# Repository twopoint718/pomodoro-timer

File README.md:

Pomodoro Timer
==============

A desktop pomodoro timer.

Peripherals
-----------

- [PCD8544](https://learn.adafruit.com/nokia-5110-3310-monochrome-lcd) 84x48 pixel LCD screen (SPI-based)
- [LSM6DSL](https://www.st.com/resource/en/datasheet/lsm6dsl.pdf) (PDF) iNEMO inertial module always-on 3D accelerometer and 3D gyroscope (I2C)
- TIM (General-purpose timer, onboard)
- GPIO reset button
- UART (onboard)

Code
----

I've either referenced, ported, or otherwise used these open source projects in my own:

- [Adafruit GFX Library](https://github.com/Adafruit/Adafruit-GFX-Library), [BSD License](https://github.com/adafruit/Adafruit-GFX-Library/blob/master/license.txt)
- [STMicroelectronics LSM6DSL accelerometer/gyro driver](https://github.com/STMicroelectronics/stm32-lsm6dsl), [BSD License](https://opensource.org/licenses/BSD-3-Clause)
- [STMicroelectronics HAL code](https://www.st.com/resource/en/user_manual/um1884-description-of-stm32l4l4-hal-and-lowlayer-drivers-stmicroelectronics.pdf) (PDF)
- [8x8 VGA Font](https://github.com/dhepper/font8x8), Public Domain License

Building
--------

Be sure to have already installed the [Arm GNU Toolchain](https://developer.arm.com/tools-and-software/open-source-software/developer-tools/gnu-toolchain).
Then this project can be built by the Makefile in the root directory.

```
make -j
```

Building under Windows
----------------------

TODO

Presentations
-------------

- 8LU Keynote by Chris Wilson: Embedded–From the point of view of a web developer
  [YouTube Link](https://youtu.be/wSTIfWqJzPw)

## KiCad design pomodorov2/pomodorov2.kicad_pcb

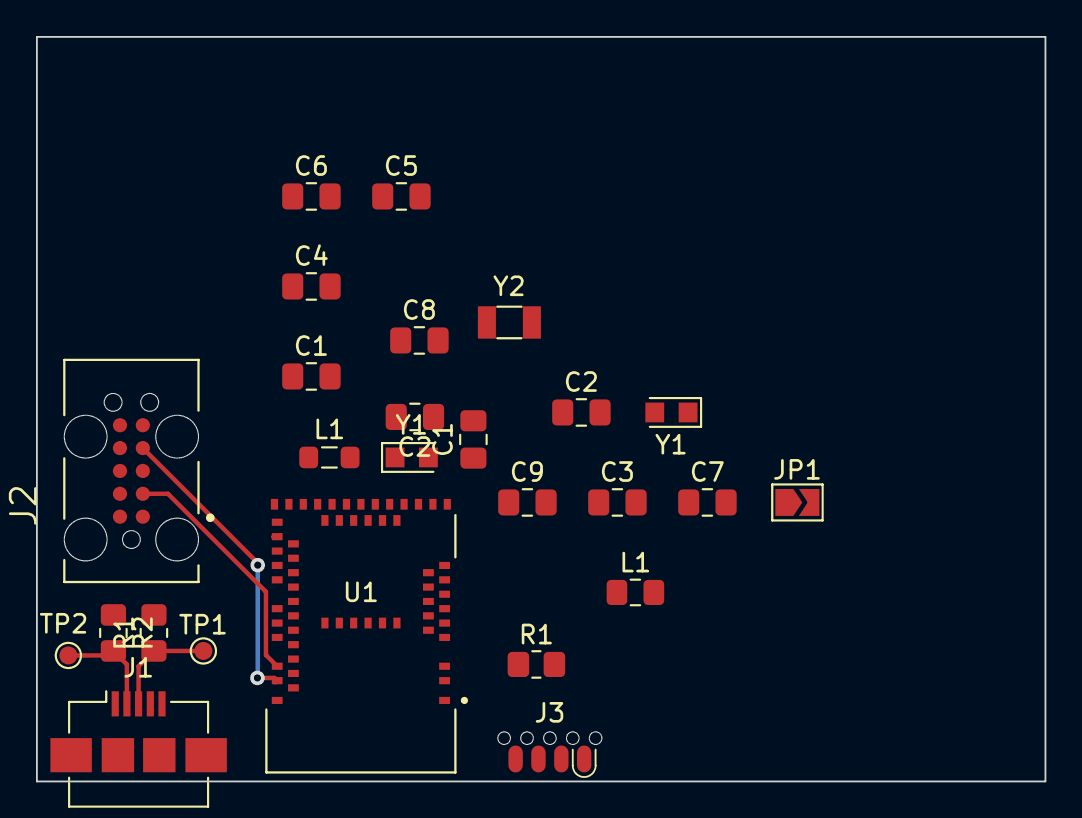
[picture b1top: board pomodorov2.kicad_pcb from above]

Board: 2 copper layers, 56.0 x 41.4 mm, 26 parts (0 on the bottom side), 18 nets.

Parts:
C1, C2, C8, C9: 12pF; C_0805_2012Metric_Pad1.18x1.45mm_HandSolder
C1#2, C2#2: 22pF; C_0805_2012Metric_Pad1.18x1.45mm_HandSolder
C3: 0.8pF; C_0805_2012Metric_Pad1.18x1.45mm_HandSolder
C4, C7: 100nF; C_0805_2012Metric_Pad1.18x1.45mm_HandSolder
C5: 100pF; C_0805_2012Metric_Pad1.18x1.45mm_HandSolder
C6: 1.0uF; C_0805_2012Metric_Pad1.18x1.45mm_HandSolder
J1: USB_B_Micro; USB_Micro-B_Amphenol_10104110_Horizontal
J2: TC2050-IDC; TAG-CONNECT_TC2050-IDC
J3: SOICbite; SOIC_clipProgSmall
JP1: SolderJumper_2_Open; SolderJumper-2_P1.3mm_Open_TrianglePad1.0x1.5mm
L1: 3.9nH; L_0805_2012Metric_Pad1.15x1.40mm_HandSolder
L1#2: 10uH (DNP?); L_0805_2012Metric_Pad1.05x1.20mm_HandSolder
R1: 100K; R_0805_2012Metric_Pad1.20x1.40mm_HandSolder
R1#2, R2: 22; R_0805_2012Metric_Pad1.20x1.40mm_HandSolder
TP1, TP2: TestPoint; TestPoint_Pad_D1.0mm
U1: MDBT50Q-1MV2; XCVR_MDBT50Q-1MV2
Y1: 32MHz; Crystal_SMD_2012-2Pin_2.0x1.2mm_HandSoldering
Y1#2: 32.768kHz; Crystal_SMD_2012-2Pin_2.0x1.2mm_HandSoldering
Y2: 32.768kHz; Crystal_SMD_3215-2Pin_3.2x1.5mm

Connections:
/SWCLK: J2.4, J3.7, U1.53 (SWDCLK)
/SWDIO: J2.2, J3.5, U1.51 (SWDIO)
/SWO: J2.6, J3.6, U1.47 (P1.00/TRACEDATA0)
/USBD+: R1#2.2, U1.35 (D+)
/USBD-: R2.1, U1.34 (D-)
/~RESET: J2.10, J3.8, U1.40 (P0.18/~RESET)
GND: C1.1, C1#2.1, C2.1, C2#2.1, C3.2, C4.1, C5.1, C6.1, C7.2, C8.2, C9.2, J1.5 (GND), J2.3, J2.5, J3.4, JP1.1 (A), U1.1 (GND), U1.2 (GND), U1.15 (GND), U1.33 (GND), U1.55 (GND)
unnamed: C1#2.2, U1.17 (P0.00/XL1), Y1#2.2
unnamed: C2#2.2, U1.18 (P0.01/XL2), Y1#2.1
unnamed: J1.2 (D-), R2.2, TP2.1
unnamed: J1.3 (D+), R1#2.1, TP1.1
unnamed: L1#2.1, U1.31 (DCCH)
unnamed: C8.1, Y2.2
unnamed: C9.1, Y2.1
unnamed: C3.1, L1.2
unnamed: C1.2, Y1.2
unnamed: C2.2, Y1.1
VCC: J2.1, J3.1, L1#2.2, R1.2, U1.28 (VDD), U1.30 (VDDH)

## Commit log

2022-01-02 Ignore compilation artifacts
2022-01-02 Configure SPI
2022-01-03 WIP: adding PCD8544 driver
2022-01-05 Add the LCD "Reset", "D/C (Data/Command)" pins
2022-01-05 WIP: display driver
2022-01-05 Configure LCD_CS pin
2022-01-06 WIP: porting Adafruit PCD8544 to work with HAL
2022-01-08 WIP: basic drawing features are present
2022-01-09 WIP: add drawing code
2022-01-09 WIP: adjust code so it compiles in new project
2022-01-10 Switch to "pair of .c/.h files" for gen'd peripherals
    - Adds
    - gpio.h/.c
    - spi.h/.c
2022-01-10 Move LCD code after peripheral init
2022-01-14 Add LCD_invertDisplay()
2022-01-14 Drop LCD_CS GPIO and use hardware SPI NSS pin
2022-01-14 Add more display code in main()
2022-01-14 Fix bug in LCD_display() loop! Eek.
2022-01-17 Set SPI data size to 8bit, slower speed
2022-01-18 modifications
2022-01-19 Simplify LCD_display()
2022-01-19 WIP tidy, changes, debugging
2022-01-19 ignore docs
2022-01-20 Fix SPI timeout
2022-01-21 Drew a circle\!
2022-01-23 Add host GCC/MacOS target
2022-01-24 Add LSM6DSL driver from Mbed example project
2022-01-25 Update README with software section
2022-01-25 Integrate LSM6DSL Driver code
    - Enable UART
    - Add some Mbed OS/BSP code for IoT01 board
    - Add accel/gyro driver code
    - Move accelero/gyro under new `Components` directory
2022-01-25 WIP: enable I2C2
    - Looks like some of my custom code got bulldozed, plz check on it
    🐍 no step on snek!
2022-01-27 Enable UART4 (TX PA0, RX PA1)
2022-01-28 Enable USB CDC (virtual com port)
2022-01-29 Remove UART
2022-01-29 Revert "Remove UART"
    ea29b3df27829001520359648c1781bb758fe39b
2022-01-31 Provide the USB CDC interface
2022-01-31 USB is hard 🤯
2022-02-03 WIP: USB debugging
2022-02-04 Changes?
2022-02-06 Remove USB support/middleware 🔌
2022-02-06 Cleanup leftover USB code
2022-02-07 Successful UART test! ⌨️
2022-02-07 Update readme with STM HAL 💾
2022-02-07 typo
2022-02-08 Add case design
2022-02-09 Design case in OpenSCAD
2022-02-10 WIP: add Adafruit 5x7 ascii font
2022-02-10 Lower the number of facets for curves
2022-02-10 WIP: Modify font code
2022-02-10 Add project-specific formatting rules for Eclipse
2022-02-11 Add & modify Adafruit `draw_char` 🔤
2022-02-11 README formatting
2022-02-11 Fix build issue
2022-02-12 Case design improvements 📐
2022-02-14 Fix dangling `{`, refactor includes
2022-02-14 Add 8x8 font
2022-02-15 Add 8x8 font-drawing routines 🖋
2022-02-15 WIP: starting on states & functions
2022-02-16 Enable TIM2 general-purpose timer ⏰
2022-02-17 Enable reloading the timer preload value ♻️
2022-02-17 Add `draw_clear_rect` function 🆑
2022-02-17 Set counter 80 million, interrupt period = 1sec
2022-02-17 Counter demo that uses timer interrupt! ⏲
2022-02-17 Start the TIM callback interrupt ⏱
2022-02-17 Flat case drawing, suitable for cutting ✂️
2022-02-18 Read and display accelerometer data 🎢
2022-02-18 A "flat-pack" case design for laser cutting ⚡️🔦
2022-02-18 Redesign as connected polygons 🔺
2022-02-18 WIP: sketching out the state machine 🤖
2022-02-19 Enable I²C Event Interrupts
2022-02-20 WIP: fill out state machine, add orientation 🔝
2022-02-20 Finish `get_orientation` ↖️⬇️↗️
2022-02-20 Refactor states, debug state machine 🔧
2022-02-21 Set `USER` button as GPIO Input 🕹
2022-02-21 Configure `USER` button as an interrupt ⚠️
2022-02-21 And generate the actual EXT interrupt handler 😓
    - Need to check the box in the config tool to generate
    `EXTI15_10_IRQHandler` which in turn calls
    `HAL_GPIO_EXTI_IRQHandler(GPIO_PIN_13)`
2022-02-21 Handle `USER` button press (reset/cancel timer) 🚫
2022-02-21 Display time, log orientation changes 🔁
2022-02-23 Add fritzing sketch
2022-02-24 Model the app in QM
2022-02-24 Rename Blinky -> Pomodoro & generate code
2022-02-24 config file
2022-02-25 Get rid of "Blinky" 💡
2022-02-25 Clean up warnings
2022-02-25 Clean up (almost) all warnings, tweak diagram 🧬
2022-02-27 Add exit actions
2022-02-28 Stop tracking `.pomodoro-timer` GUI file
2022-03-03 Add case rendering 📸
2022-03-04 Add `num_poms` attr and increment attr (🍅++)
2022-03-07 Add release build directory 🚫
2022-03-09 WIP, build using makefile 📝
2022-03-10 Replace main with model/main 🪢
2022-03-11 Add headless build script 🎃
2022-03-11 WIP, Makefile surgery 👩🏼‍⚕️
2022-03-14 WIP: makefile 🗒
2022-03-14 WIP: Re-write Makefile to combine projects ♻️
2022-03-15 WIP: continue Makefile/build refactor 👻
2022-03-16 WIP: Even more Makefile tweaking 🔧
2022-03-16 WIP: Change to QV Cooperative Kernel. Add VSCode config 👯‍♀️
2022-03-19 Add build section to readme 👷‍♂️
2022-03-20 Tweak cpp properties file for vscode
2022-03-21 WIP: getting a clean build. Test. 🧼
2022-04-01 Add KiCad project
2022-04-03 Add some more parts to the v2 board 🔶
2022-04-04 Remove cortex header
    - remove main cortex header
    - tag-connect remains
    - soicbite remains
2022-04-05 Add components for chip, no routing 🚏
2022-04-07 Add Adafruit MDBT50Q-1MV2, remove nRF52832 QFN 🔄
2022-04-08 Adding test points, usb, crystals 💎
2022-04-09 Make schematic more legible 👓
2022-04-10 A little routing and schematic cleanup 🧹
2022-04-11 Some layout, schematic work 👷‍♂️
2022-04-12 Add Stemma connector, add signals 📶
2022-04-16 Add YouTube link 🎥
2022-04-18 Populate parts on board, remove stemma conn 🪓
2022-04-20 Add section about building in Windows
2022-04-30 Change to YouTube direct link 🔗
2022-08-19 Migrate PCB project to pomodorov2 repo
